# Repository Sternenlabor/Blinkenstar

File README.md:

# Blinkenstar

## Overview

This repository contains the Blinkenstar hardware design, AVR firmware, and Node-based bench tools used to validate audio transfer reception and stored playback on the board.

## Docs

- [Docs Index](./docs/README.md)
- [Getting Started](./docs/getting-started.md)
- [Firmware Guide](./docs/firmware.md)
- [Board Usage](./docs/board-usage.md)
- [Bench And Debug](./docs/bench-and-debug.md)
- [Hardware Guide](./docs/hardware.md)
- [Development Guide](./docs/development.md)

## Quick Start

Install dependencies and run the default checks:

```bash
npm install
npm test
```

Build the main firmware:

```bash
cd firmware
pio run -e release
```

## Firmware Environments

The public PlatformIO environments are:

- `release`: normal RX/store firmware for the board
- `debugwire`: the same RX/store firmware, built for debugWIRE
- `jp1debug`: RX diagnostic firmware with TX-only JP1 serial logs
- `hwdiag`: button/display hardware diagnostic firmware

See [Firmware Guide](./docs/firmware.md) for the current behavior and caveats of each environment.

## Bench Commands

Continuous sine-wave audio path check:

```bash
npm run tone:test
```

One-shot framed transfer playback:

```bash
npm run transfer:test
```

See [Bench And Debug](./docs/bench-and-debug.md) for JP1 wiring, diagnostic images, and recommended bring-up order.

## License

Blinkenstar uses separate licenses for separate repository parts:

- Hardware design files in `hardware/Blinkenstar/`: CERN Open Hardware Licence Version 1.2 (`CERN-OHL-1.2`)
- Firmware in `firmware/`: GNU Lesser General Public License Version 3.0 (`LGPL-3.0-only`)
- Documentation, instructions, and Blinkenstar images: Creative Commons Attribution-ShareAlike 4.0 International (`CC-BY-SA-4.0`)
- Node bench utilities and host-side tests in `scripts/` and `test/`: MIT License

See [`LICENSE`](./LICENSE) for the full repository licensing overview and attribution notes.

## JP1 Wiring

JP1 serial wiring for `jp1debug`:

- Build: `PLATFORMIO_CORE_DIR=/tmp/pio-core ~/.platformio/penv/bin/pio run -e jp1debug`
- `JP1 pin 2` (`E1`, `PC0`) is debug TX
- `JP1 pin 4` is GND
- Connect a USB-UART adapter `RX` to `JP1 pin 2`
- Connect adapter `GND` to `JP1 pin 4`

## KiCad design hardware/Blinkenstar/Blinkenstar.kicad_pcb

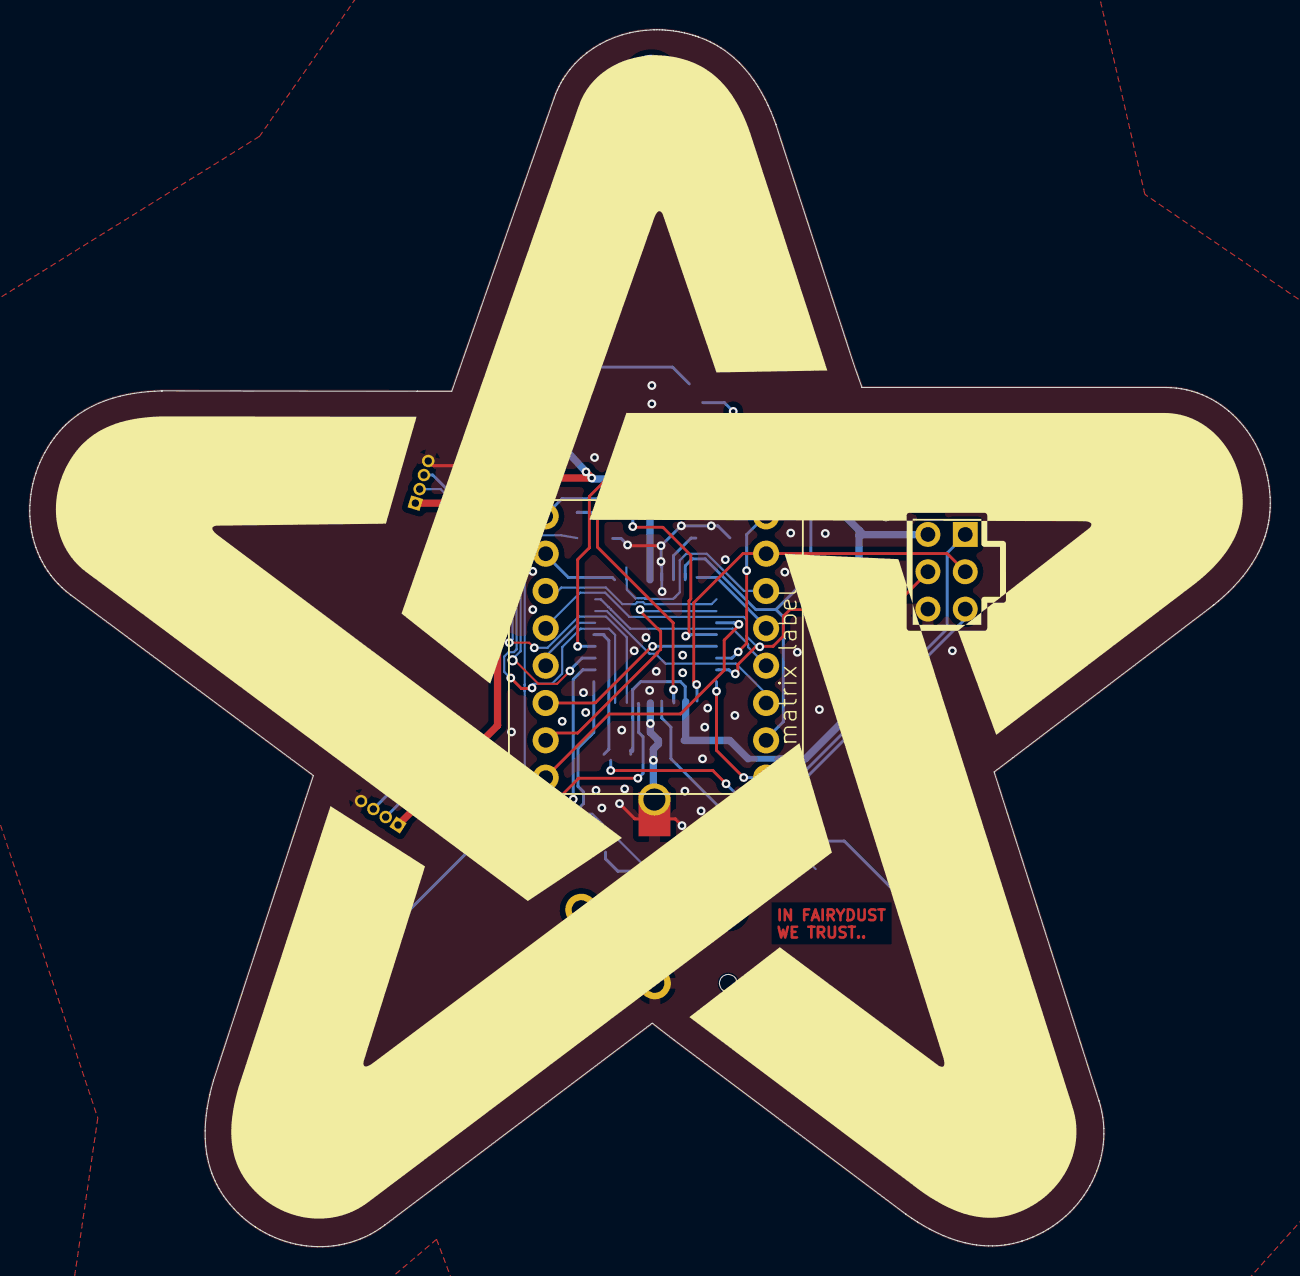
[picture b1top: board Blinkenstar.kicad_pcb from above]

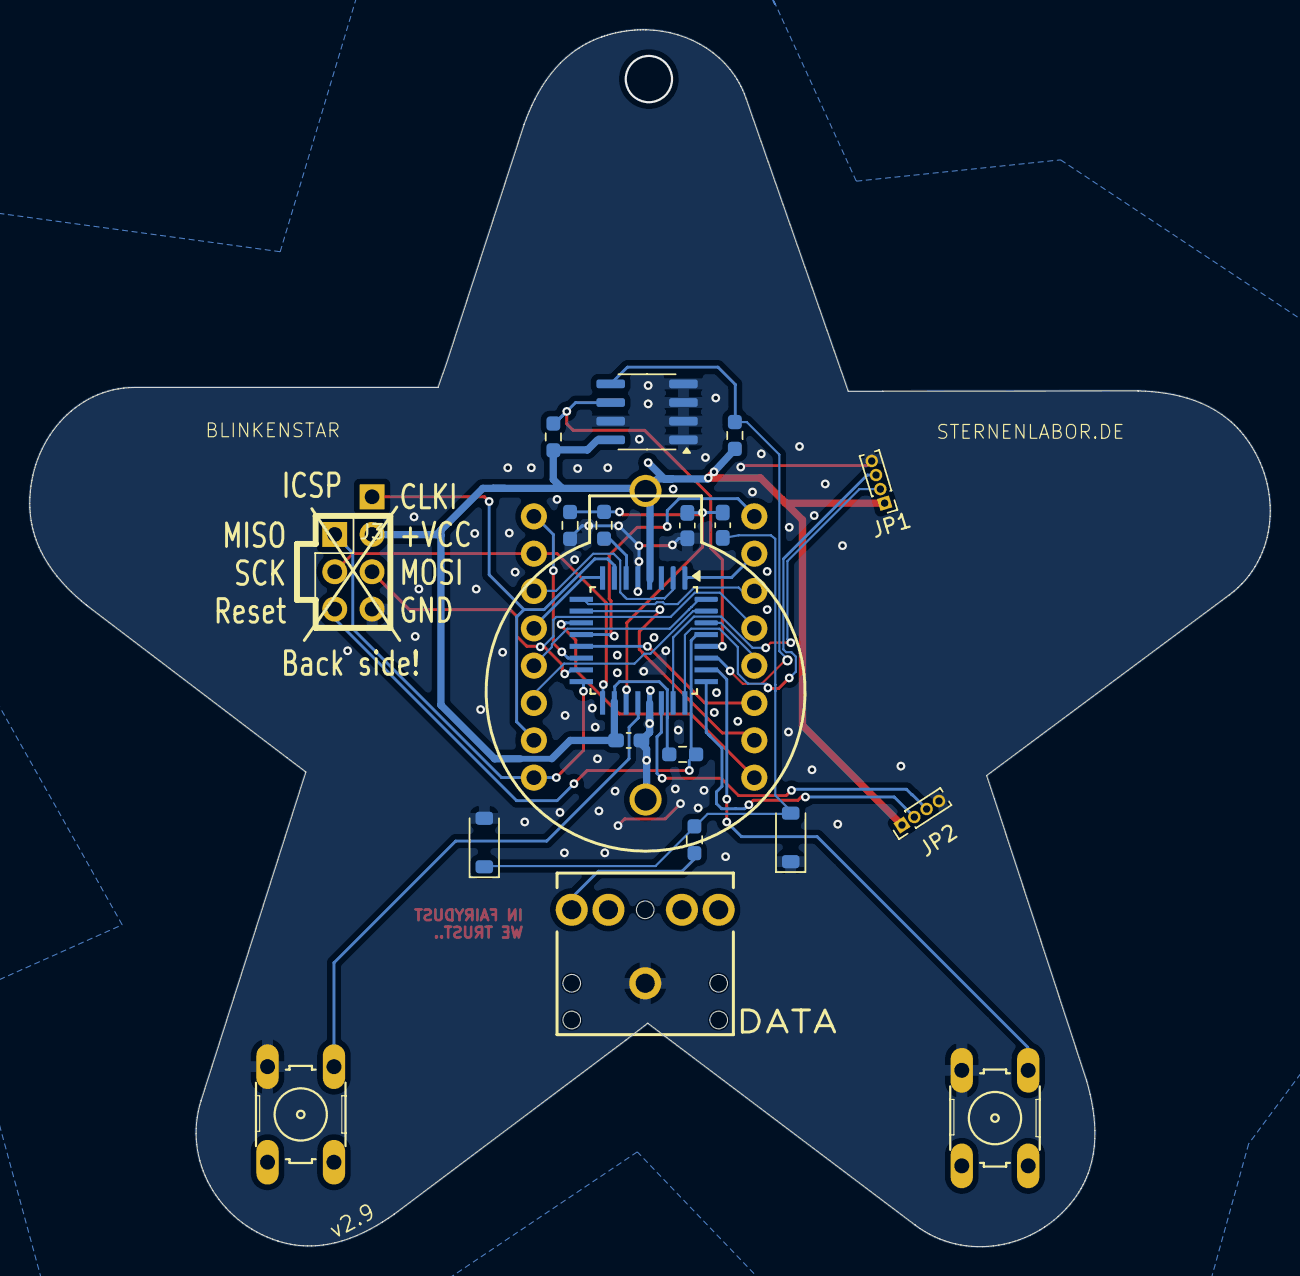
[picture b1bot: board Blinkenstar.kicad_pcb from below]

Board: 2 copper layers, 84.4 x 82.8 mm, 22 parts (21 on the bottom side), 31 nets.

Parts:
BT1: Battery_Cell; CR2032PAC_ELECTRODRAGON
C1: 10uF; C_0603_1608Metric_Pad1.08x0.95mm_HandSolder
C2, C3: 0.47uF; C_0603_1608Metric_Pad1.08x0.95mm_HandSolder
D1, D2: 1N4148W; D_SOD-123
ISP1: AVR-ISP-6VERT; PinHeader_2x03_P2.54mm_Vertical
J1: AudioJack2_Ground; AUDIO-JACK
J3: CLKI; PinHeader_1x01_P2.54mm_Vertical
JP1, JP2: PINHD-1X04_2.54-S; PinHeader_1x04_P1.00mm_Vertical
LED1: SEGMENT_8X8_ROWCATHODEM12A881UR; SEGMENT_BL-M12A883
R1: 16; R_0603_1608Metric_Pad0.98x0.95mm_HandSolder
R2: 8.2K; R_0603_1608Metric_Pad0.98x0.95mm_HandSolder
R3: 6.8K; R_0603_1608Metric_Pad0.98x0.95mm_HandSolder
R4, R5, R6: 10K; R_0603_1608Metric_Pad0.98x0.95mm_HandSolder
S1, S2: B3F-1000; B3F-10XX
U2: ATtiny88-A; TQFP-32_7x7mm_P0.8mm
U3: EEPROM-I2CEIAJ; SOIC-8_3.9x4.9mm_P1.27mm

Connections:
/AVR_AUDIO_IN: C1.2, C2.1, R2.1, R3.2, U2.19 (PA0)
/B1: S1.1, U2.20 (PC7)
/B2: S2.1, U2.26 (PC3)
/C1: LED1.13 (A1), U2.30 (PD0)
/C2: LED1.3 (A2), U2.31 (PD1)
/C3: LED1.4 (A3), U2.32 (PD2)
/C4: LED1.10 (A4), U2.1 (PD3)
/C5: LED1.6 (A5), U2.2 (PD4)
/C6: LED1.11 (A6), U2.9 (PD5)
/C7: LED1.15 (A7), U2.10 (PD6)
/C8: LED1.16 (A8), U2.11 (PD7)
/E1: JP1.2, U2.23 (PC0)
/E2: JP1.3, U2.24 (PC1)
/E3: JP2.2, U2.25 (PC2)
/E4: JP2.3, U2.22 (PA1)
/R1: LED1.9 (K1), U2.12 (PB0)
/R2: LED1.14 (K2), U2.13 (PB1)
/R3: LED1.8 (K3), U2.14 (PB2)
/R4/MOSI: ISP1.4, LED1.12 (K4), U2.15 (PB3)
/R5/MISO: ISP1.1, LED1.1 (K5), U2.16 (PB4)
/R6/SCK: ISP1.3, LED1.7 (K6), U2.17 (PB5)
/R7/CLKI: J3.1, LED1.2 (K7), U2.7 (PB6)
/R8: LED1.5 (K8), U2.8 (PB7)
/RESET: ISP1.5, R4.1, U2.29 (~RESET/PC6)
/SCL: R5.2, U2.28 (PC5), U3.6 (SCL)
/SDA: R6.2, U2.27 (PC4), U3.5 (SDA)
/TRIG2: R2.2, U2.6 (PA3)
GND: BT1.2 (-), C2.2, C3.2, D1.1 (K), D2.2 (A), ISP1.6, J1.SLEEVE, JP1.4, JP2.4, R3.1, S1.3, S2.3, U2.5 (GND), U2.21 (GND), U3.1 (A0), U3.2 (A1), U3.3 (A2), U3.4 (GND), U3.7 (WP)
unnamed: C1.1, D1.2 (A), D2.1 (K), R1.1
unnamed: J1.RING, R1.2
VCC: BT1.1 (+), C3.1, ISP1.2, JP1.1, JP2.1, R4.2, R5.1, R6.1, U2.4 (VCC), U2.18 (AVCC), U3.8 (VCC)

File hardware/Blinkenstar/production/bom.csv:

Designator,Footprint,Quantity,Value,LCSC Part #
BT1,CR2032PAC_ELECTRODRAGON,1,Battery_Cell,C19184089
C1,0603,1,10uF,C19702
"C2, C3",0603,2,0.47uF,C1623
"D1, D2",D_SOD-123,2,1N4148W,C7420318
ISP1,PinHeader_2x03_P2.54mm_Vertical,1,AVR-ISP-6VERT,
J1,AUDIO-JACK,1,AudioJack2_Ground,C16684
J3,PinHeader_1x01_P2.54mm_Vertical,1,CLKI,
"JP1, JP2",PinHeader_1x04_P1.00mm_Vertical,2,PINHD-1X04_2.54-S,
LED1,SEGMENT_BL-M12A883,1,SEGMENT_8X8_ROWCATHODEM12A881UR,
R1,0603,1,16,C217814
R2,0603,1,8.2K,C25981
R3,0603,1,6.8K,C23212
"R4, R5, R6",0603,3,10K,C25804
"S1, S2",B3F-10XX,2,B3F-1000,C393938
U2,TQFP-32_7x7mm_P0.8mm,1,ATtiny88-A,C111451
U3,SOIC-8_3.9x4.9mm_P1.27mm,1,EEPROM-I2CEIAJ,C79988

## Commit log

2025-03-28 ༼ つ ◕_◕ ༽つ in fairy dust we trust..
2025-03-28 remove temp files
2025-03-28 ignore all temp files
2025-03-28 added firmware
2025-03-28 added 3D models
2025-03-28 added images
2025-03-28 add unasembled image
2025-03-28 image update
2025-03-28 close prj
2025-03-31 better ICSP layout
2025-04-10 enhance pad size for MCU soldering
2025-06-01 initial work on firmware
2025-06-02 Change Display refresh rate to 60 Hz
2025-06-20 fix GND issue
2025-08-28 Adds CLKI connector for clock input
    Adds a single-pin connector for external clock input (CLKI).
    This enables the Blinkenstar to synchronize with an external clock source.
    Also sets 'exclude_from_bom' and 'dnp' attributes to the test point components.
2025-08-28 Adds modem receiver and diagnostics
    Implements a receive-only audio modem with FEC. The modem
    demodulates audio input from the ADC, applies Hamming(24,16)
    forward error correction, and stores decoded bytes into flash
    memory via the existing Storage class.
    Adds simple diagnostics mode enabled by build flags, allowing
    testing of the display hardware by directly controlling
2026-04-02 test: add sine wave generator coverage
2026-04-02 docs: document audio test tone usage
2026-04-02 feat: add audio test tone runner
2026-04-03 feat: add audio output and sine wave generation functionality
    - Implemented audio output capabilities with the Speaker module.
    - Created functions for generating and playing sine wave PCM audio.
    - Added transfer tone encoding and playback features.
    - Developed tests for audio output, sine wave generation, and transfer tone encoding.
    - Ensured all scripts are in ES module format and removed legacy .js files.
    - Updated package.json to include new test scripts for audio functionalities.
2026-04-03 refactor: migrate codebase to ESM modules and update related documentation
2026-04-03 feat: implement boot message rendering and state preservation during shutdown
2026-04-04 feat: enhance display state management with boot message restoration and freezing functionality
2026-04-04 feat(modem): enhance ADC handling and diagnostics logging
    - Added static methods in Modem.h for ADC digital input mask and conversion start.
    - Implemented payload buffer display logic in Receiver.cpp for showing stored patterns.
    - Introduced diagnostic logging functionality in Receiver for tracking state transitions and events.
    - Updated System initialization to capture and log reset causes, with options for headless RX diagnostics.
    - Refactored platformio.ini to streamline build flags and ensure legacy modem configurations are used.
    - Added tests for modem ADC configurations, legacy demodulator behavior, receiver frame completion guards, and reset cause diagnostics.
2026-04-04 feat: update display refresh timing and enhance EEPROM write timing tests
2026-04-05 feat: implement full rename of legacy identifiers to blinkenstar
    - Added a comprehensive plan and design document for renaming all instances of `rocket` and `Blinkenrocket` to `blinkenstar` and `Blinkenstar` across firmware, documentation, and KiCad files.
    - Created regression tests to ensure the rename does not alter existing behavior.
    - Refactored firmware code to replace legacy identifiers with the new naming convention.
    - Updated KiCad library identifiers and local asset filenames to reflect the new naming.
    - Ensured all changes are covered by tests and verified through the existing build and test processes.
    refactor: separate TwiBus from Storage
2026-04-05 feat: rename legacy identifiers to blinkenstar and update related tests
2026-04-05 feat: implement factory reset functionality and add corresponding tests
2026-04-05 feat: add upstream flashing animation display and corresponding test
2026-04-05 feat: update README and add documentation for hardware, firmware, and usage guides
2026-04-05 Remove speaker module and its examples, types, and tests
    - Deleted the speaker module implementation including all associated files such as examples, type definitions, and tests.
    - This includes the removal of sine wave generation example, stdin piping example, and the main speaker functionality.
    - All related files in the 'src', 'test', and 'examples' directories have been removed to clean up the repository.
2026-04-05 feat(display): add support for storage-backed animations with chunk loading
    - Introduced `startAnimation_` method to handle both regular and storage-backed animations.
    - Added `showFromStorage` method to initiate animations that can be loaded in chunks from EEPROM.
    - Implemented chunk loading logic in `ensureStorageChunkLoaded_` and `chunkOffset_` methods.
    - Updated `update` method to handle chunked data for both frame and text animations.
    - Modified `snapshotState` and `restoreState` to track and restore storage-backed animation state.
    - Adjusted `showPayloadBuffer` in `Receiver.cpp` to differentiate between regular and storage-backed animations.
2026-04-05 feat(buttons): implement button browse locking mechanism to prevent contact bounce
2026-04-07 Enhance transfer handling and debugging features
    - Update documentation to clarify behavior for stalled transfers and error handling.
    - Modify the board usage documentation to reflect timeout behavior for incomplete frames.
    - Improve firmware structure by adding timeout recovery for interrupted transfers in the modem receiver.
    - Refactor display logic to support animation rewind and repeat handling.
    - Implement debug logging conditionally based on configuration flags.
    - Introduce new tests to verify the correct handling of animation boundaries and interrupted transfer timeouts.
2026-04-07 docs(firmware): document intentional upstream difference in MCU sleep behavior
2026-04-07 refactor(firmware): update flash helpers and remove legacy script
2026-04-23 fix: restore release transfer persistence
2026-05-13 feat: Add Blinkenstar hardware and comprehensive documentation
    - Integrate the Blinkenstar hardware design files, including KiCad project data and related assets.
    - Introduce two versions of the buildable Blinkenstar manual in Markdown format.
    - Implement a Node.js-based script for generating PDF manuals from Markdown, complete with image and text reflow capabilities.
    - Update the project's licensing to a granular structure, specifying licenses for hardware (CERN-OHL-1.2), firmware (LGPL-3.0-only), documentation (CC-BY-SA-4.0), and host utilities (MIT).
    - Update the README to reflect the new licensing overview.
2026-05-13 feat: Add PCB Styler project archive
2026-05-13 docs: Organize manual images and correct content
    - Relocates images specific to the 'ohne-smd' manual into their own subdirectory for better asset management.
    - Corrects minor grammatical errors in the German text of both the standard and 'ohne-smd' manuals.
    - Removes unused metadata entries from the Markdown source files.
    - Regenerates the PDF versions to reflect these changes.
2026-05-13 docs: Update manual 'About' section and PDF text block parsing
    - Remove outdated information regarding Blinkenstar V2 and its availability.
    - Adjust the 'About Blinkenstar' text block layout (width, font size, line height) for improved presentation.
    - Refine the PDF generation script to correctly process multi-paragraph Markdown content within a single text block.
    - Add tests to ensure proper text block parsing and layout adherence.
2026-05-14 feat: Refine system interaction and modem reliability
    - Invert stored pattern navigation button logic for improved user experience.
    - Implement a two-button chord for waking from deep sleep, preventing accidental wake-ups.
    - Ensure the FEC modem's state is cleared on initialization and report buffered decoded bytes immediately.
    - Restart the modem receiver after ADC power is restored during system wake-up.
    - Update KiCad project files and revise silkscreen elements for the latest hardware revision.
2026-05-14 Update Blinkenstar configuration and production files
    - Added "OPEN BROWSER" and "NO_BACKUP_OPT" options to fabrication-toolkit-options.json.
    - Introduced new production zip file Blinkenstar_2.9.zip.
    - Created backup zip file Blinkenstar_2.9_2026-05-14_22-12-31.zip.
    - Modified netlist.ipc to update VIA connections, replacing several with new identifiers and removing obsolete entries.
    - Adjusted J1 connections in netlist.ipc for improved clarity and accuracy.
